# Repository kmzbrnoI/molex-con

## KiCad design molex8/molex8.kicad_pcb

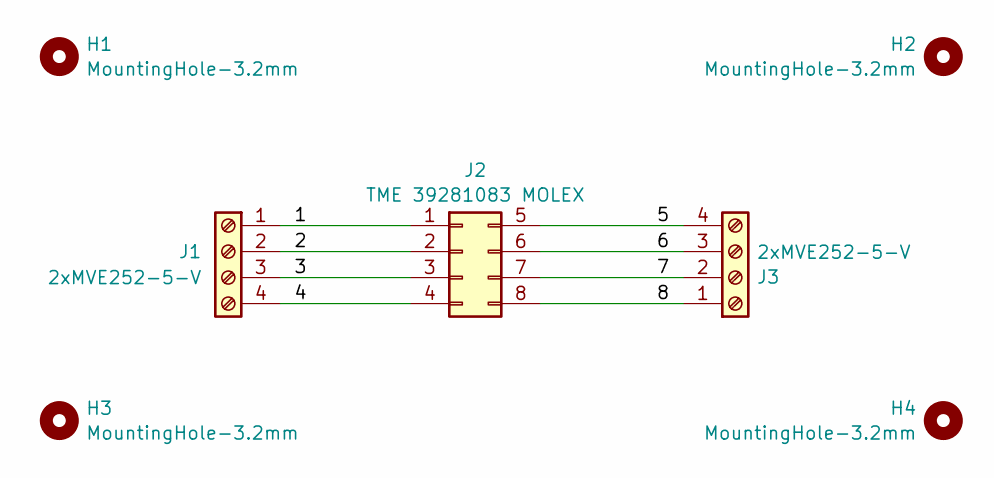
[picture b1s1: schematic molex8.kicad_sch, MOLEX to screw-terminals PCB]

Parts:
H1, H2, H3, H4: MountingHole-3.2mm; MountingHole_3.2mm_M3_Pad
J1, J3: 2xMVE252-5-V; MVE252-5-V-2x
J2: TME 39281083 MOLEX; Molex_Mini-Fit_Jr_5566-08A2_2x04_P4.20mm_Vertical

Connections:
/1: J1.1, J2.1
/2: J1.2, J2.2
/3: J1.3, J2.3
/4: J1.4, J2.4
/5: J2.5, J3.4
/6: J2.6, J3.3
/7: J2.7, J3.2
/8: J2.8, J3.1

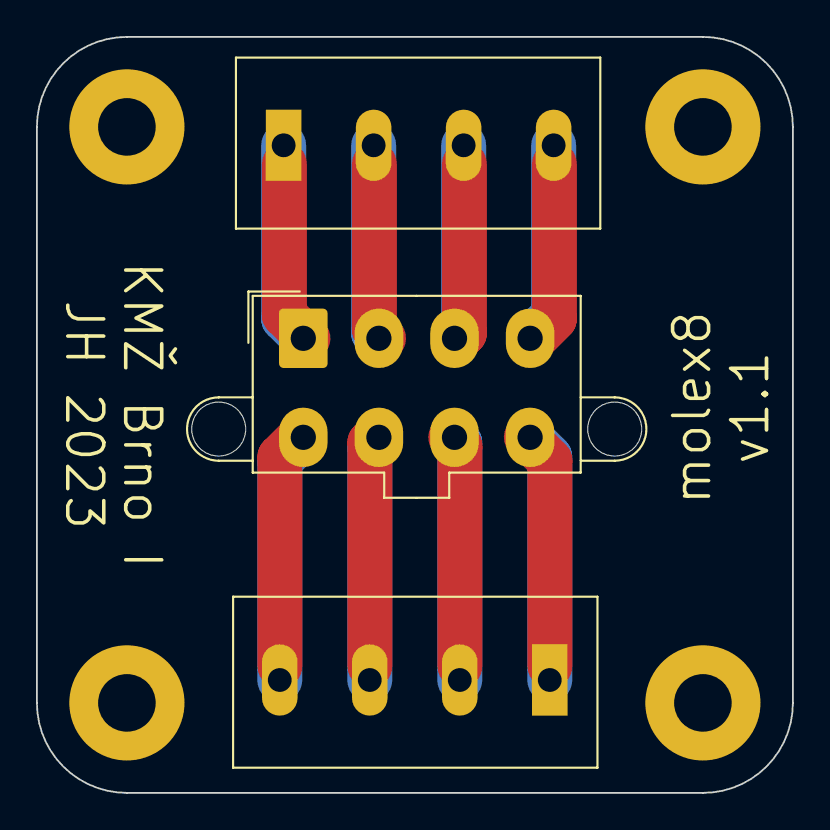
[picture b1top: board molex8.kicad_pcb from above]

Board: 2 copper layers, 42.0 x 42.0 mm, 7 parts (0 on the bottom side), 8 nets.

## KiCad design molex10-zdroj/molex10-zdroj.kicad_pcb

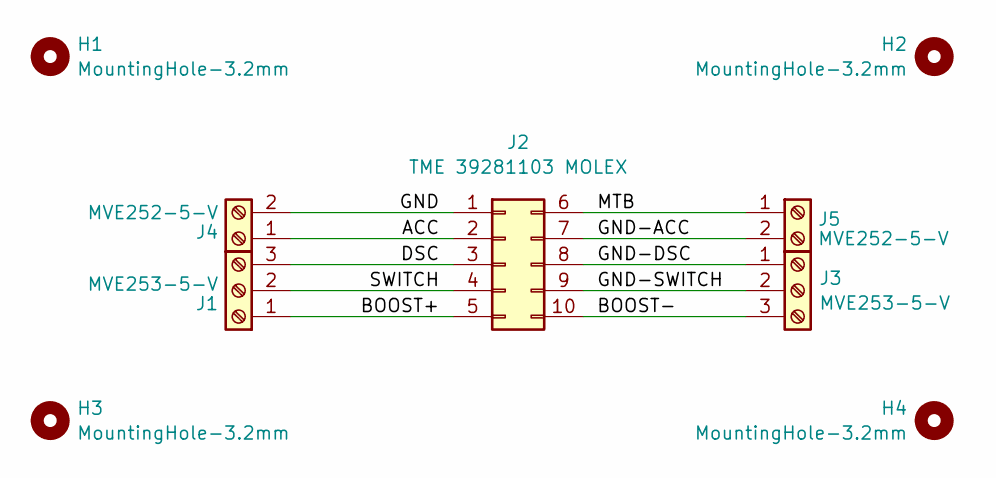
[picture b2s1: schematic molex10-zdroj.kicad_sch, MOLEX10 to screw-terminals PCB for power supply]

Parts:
H1, H2, H3, H4: MountingHole-3.2mm; MountingHole_3.2mm_M3_Pad
J1, J3: MVE253-5-V
J2: TME 39281103 MOLEX; Molex_Mini-Fit_Jr_5566-10A2_2x05_P4.20mm_Vertical
J4, J5: MVE252-5-V

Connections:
/ACC: J2.2, J4.1
/BOOST+: J1.1, J2.5
/BOOST-: J2.10, J3.3
/DSC: J1.3, J2.3
/GND: J2.1, J4.2
/GND-ACC: J2.7, J5.2
/GND-DSC: J2.8, J3.1
/GND-SWITCH: J2.9, J3.2
/MTB: J2.6, J5.1
/SWITCH: J1.2, J2.4

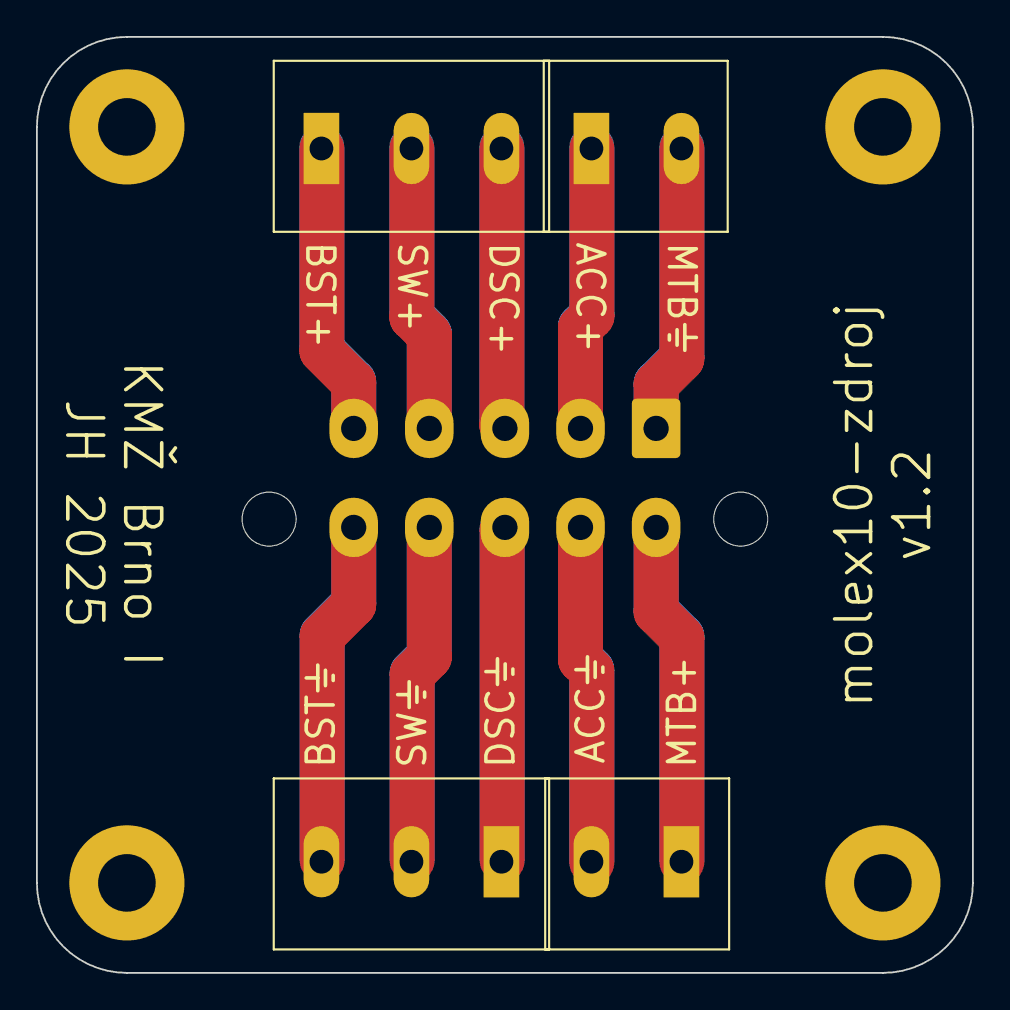
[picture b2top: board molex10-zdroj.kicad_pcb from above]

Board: 2 copper layers, 52.0 x 52.0 mm, 9 parts (1 on the bottom side), 10 nets.

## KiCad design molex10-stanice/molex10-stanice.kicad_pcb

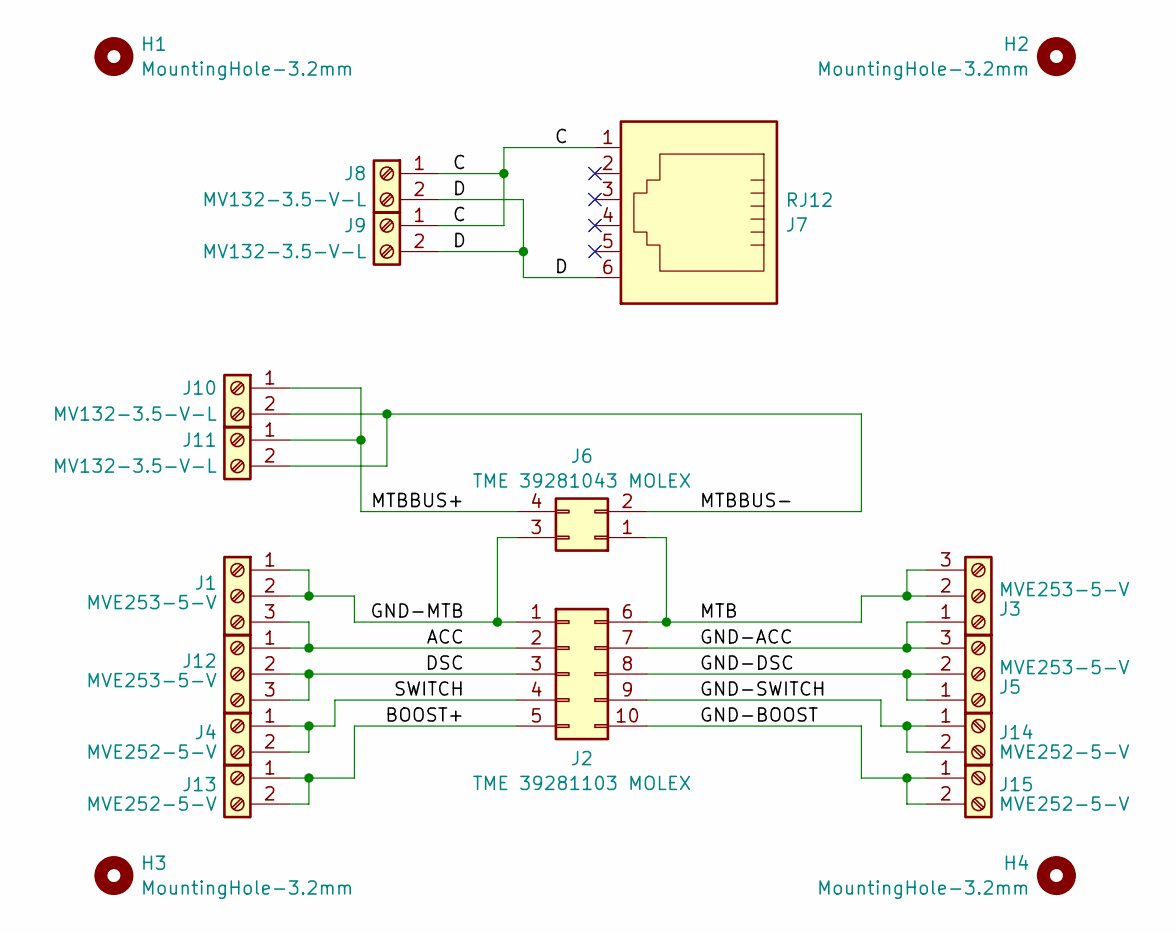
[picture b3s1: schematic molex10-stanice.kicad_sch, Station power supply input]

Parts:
H1, H2, H3, H4: MountingHole-3.2mm; MountingHole_3.2mm_M3_Pad
J1, J3, J5, J12: MVE253-5-V
J2: TME 39281103 MOLEX; Molex_Mini-Fit_Jr_5566-10A2_2x05_P4.20mm_Vertical
J4, J13, J14, J15: MVE252-5-V
J6: TME 39281043 MOLEX; Molex_Mini-Fit_Jr_5566-04A_2x02_P4.20mm_Vertical
J7: RJ12; RJ25_Wayconn_MJEA-660X1_Horizontal
J8, J9, J10, J11: MV132-3.5-V-L; TerminalBlock_4Ucon_1x02_P3.50mm_Horizontal

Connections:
/ACC: J1.3, J2.2, J12.1
/BOOST+: J2.5, J13.1, J13.2
/C: J7.1, J8.1, J9.1
/D: J7.6, J8.2, J9.2
/DSC: J2.3, J12.2, J12.3
/GND-ACC: J2.7, J3.1, J5.3
/GND-BOOST: J2.10, J15.1, J15.2
/GND-DSC: J2.8, J5.1, J5.2
/GND-MTB: J1.1, J1.2, J2.1, J6.3
/GND-SWITCH: J2.9, J14.1, J14.2
/MTB: J2.6, J3.2, J3.3, J6.1
/MTBBUS+: J6.4, J10.1, J11.1
/MTBBUS-: J6.2, J10.2, J11.2
/SWITCH: J2.4, J4.1, J4.2

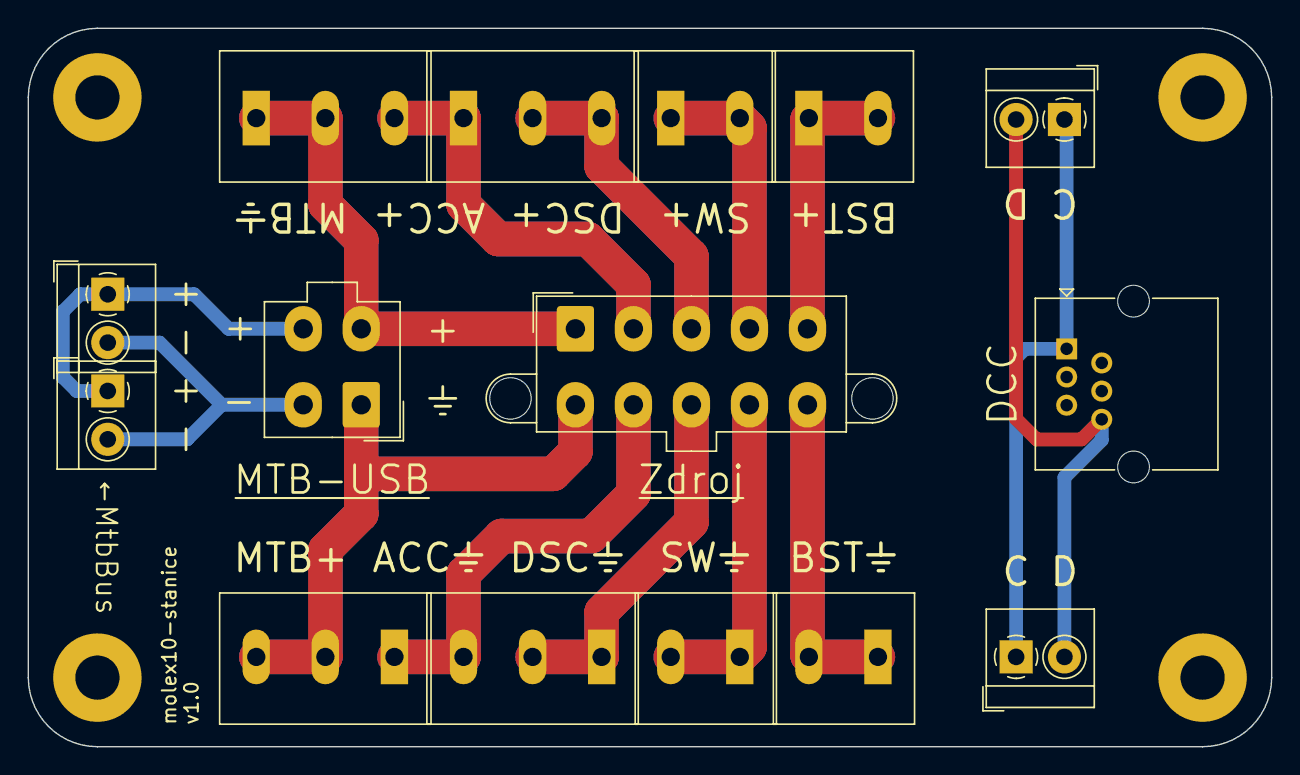
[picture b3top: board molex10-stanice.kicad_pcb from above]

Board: 2 copper layers, 90.0 x 52.0 mm, 19 parts (0 on the bottom side), 14 nets.

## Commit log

2022-12-02 Add KiCad .gitignore.
2022-12-02 Add empty KiCad project.
2022-12-02 Draw schematics, route pcb.
2022-12-02 Add makefile.
2022-12-31 Move molex8 to 'molex8' subdirectory.
2022-12-31 Customize modulovka pcb.
2022-12-31 Modulovka: makefile.
2022-12-31 Add generated files to .gitignore.
2022-12-31 molex8: fix akefile.
2022-12-31 Update silkscreen.
2023-02-15 Standardize dimensions to 42x42 mm.
2024-06-13 Add molex14 & molex18 PCBs.
2024-06-14 Add molex10-zdroj.
2024-06-15 Use screw terminal symbols, use MVE25-5-V as values.
2024-06-20 Add molex10-stanice.
2024-06-20 Do not panelize molex10-zdroj.
2024-06-25 molex10-zdroj: flip MOLEX to bottom side.
2024-06-25 molex10-stanice: slight enhancements.
2024-06-25 molex10-stanice: remove solder mask on wires.
2024-06-25 molex10: Use blue solder mask.
2024-06-25 Add note regarding PYTHONPATH.
2025-02-15 molex10-zdroj: center MOLEX connector horizontally.
    PCB v1.1
2025-04-01 molex10-zdroj: update to KiCad 9, add silkscreen desc.
2025-05-13 modulovka: migrate to KiCad 9.
2025-05-13 modulovka: name wires, fix conn symbol, fix switched 2-3.
2025-05-13 molex8: migrate to KiCad 9.
2025-05-13 molex8: add wire names.
